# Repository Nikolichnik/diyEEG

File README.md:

# diyEEG
<h4>Attempt at building DIY EEG device.</h4>

<hr>

<p align="center">

</p>

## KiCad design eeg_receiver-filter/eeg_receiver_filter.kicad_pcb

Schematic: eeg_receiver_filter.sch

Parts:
C1: 10pF
C2: 330uF
C3, C6, C7, C8, C9, C10, C11, C12: 1nF
C4, C13, C14, C15, C16: 1uF
C5, C17: 3.3nF
D1: RedHiBr
J1: USB
L1: 70nH/60nH*
P1: eeg_out
P2: CONN_1
P3: RX_out
Q1, Q2: BFR92
R1: 100k
R2, R7, R10, R13, R15, R19, R20, R21, R24, R25: 1.5M
R3, R9, R11, R12: 10k
R4, R5: 3k6
R6: 1M1
R8, R14, R23, R28: 180k
R16, R17, R18, R22, R26, R27: 30k
R29: 2k
R30: 22k
R31: 20k
R32: 200k
R33: 47k
RV1: 10k
RV2: 100k
U1: TLC274CD
U2: TLC272CD

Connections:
+5V: J1.1 (Vbus), R9.1, R11.1, RV1.3, U1.4 (V+), U2.8 (V+)
GND: C4.2, C14.2, R30.1, U1.1, U1.2 (-), U1.10 (+), U1.12 (+), U2.5 (+)
GNDPWR: J1.4 (GND), P1.2 (PM), P3.2 (PM), Q1.1 (E), Q2.1 (E), R12.2, RV1.1, RV2.1, U1.11 (V-), U2.4 (V-)
unnamed: C10.2, C11.2, R21.2, R29.1, U2.1, U2.2 (-)
unnamed: R21.1, R22.1
unnamed: R25.2, R28.1
unnamed: R24.2, R25.1
unnamed: R20.2, R23.2
unnamed: C10.1, C11.1, R23.1, R24.1
unnamed: C12.2, R28.2, U2.3 (+)
unnamed: R26.2, R27.2
unnamed: R22.2, R26.1
unnamed: C5.1, C13.1, R5.2, U1.8
unnamed: C16.2, R33.1, U1.13 (-)
unnamed: R16.2, R17.1
unnamed: R19.2, R20.1
unnamed: C13.2, C15.1, C16.1, R30.2
unnamed: C9.1, C15.2, R19.1, R33.2, U1.14
unnamed: C3.2, C8.1, R18.1
unnamed: C9.2, C12.1, R27.1
unnamed: P1.1, RV2.2
unnamed: C17.2, R32.2, U2.6 (-)
unnamed: C14.1, R29.2, R31.1, R32.1
unnamed: C17.1, R31.2, RV2.3, U2.7
unnamed: C1.2, D1.2 (K), R1.1
unnamed: R3.2, R9.2
unnamed: R1.2, RV1.2
unnamed: C2.2, C3.1, P3.1, R2.1
unnamed: R11.2, R12.1, U1.3 (+)
unnamed: C5.2, R6.2, U1.9 (-)
unnamed: C4.1, R4.2, R5.1, R6.1
unnamed: C6.2, C7.2, R4.1, R15.2, U1.6 (-), U1.7
unnamed: R15.1, R16.1
unnamed: C6.1, C7.1
unnamed: C8.2, R14.2, U1.5 (+)
unnamed: R17.2, R18.2
unnamed: C1.1, C2.1, L1.2, P2.1, Q1.3 (C), Q2.2 (B), R3.1
unnamed: R2.2, R7.1
unnamed: D1.1 (A), L1.1, Q1.2 (B), Q2.3 (C)
unnamed: R13.2, R14.1
unnamed: R10.2, R13.1
unnamed: R8.1, R10.1
unnamed: R7.2, R8.2

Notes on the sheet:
Fosc=1/(2*Pi*sqrt(L*C)) ____________________________ Unit1: C=10 pF + LED (red, HiBr 5mm) LED- (5V -> 0V) -> (2pF -> 3.6pF) Ct=(1.67pF -> 5.65pF) L=70 nF (9T, 3 mm (W), 9 mm (L)) Fosc=(369MHz -> 467MHz)
|- notch Fc=50.08Hz Hz G=1 -|
|- LPF Fc=44 Hz G=-1 -|
|- HPF Fc=4.9 Hz G=-1 -|
|- LPF Fc=43.8 Hz G=-10 -|
P1- filtered out P2- RX antenna P3- RX out_test
Unit2: C=10 pF + LED (red, HiBr 5mm) LED- (5V -> 0V) -> (2pF -> 3.6pF) Ct=(1.67pF -> 5.65pF) L=60 nF (8T, 3 mm (W), 8 mm (L)) Fosc=(399MHz -> 502MHz)
Gt=-10
|- final output curve (?) -|

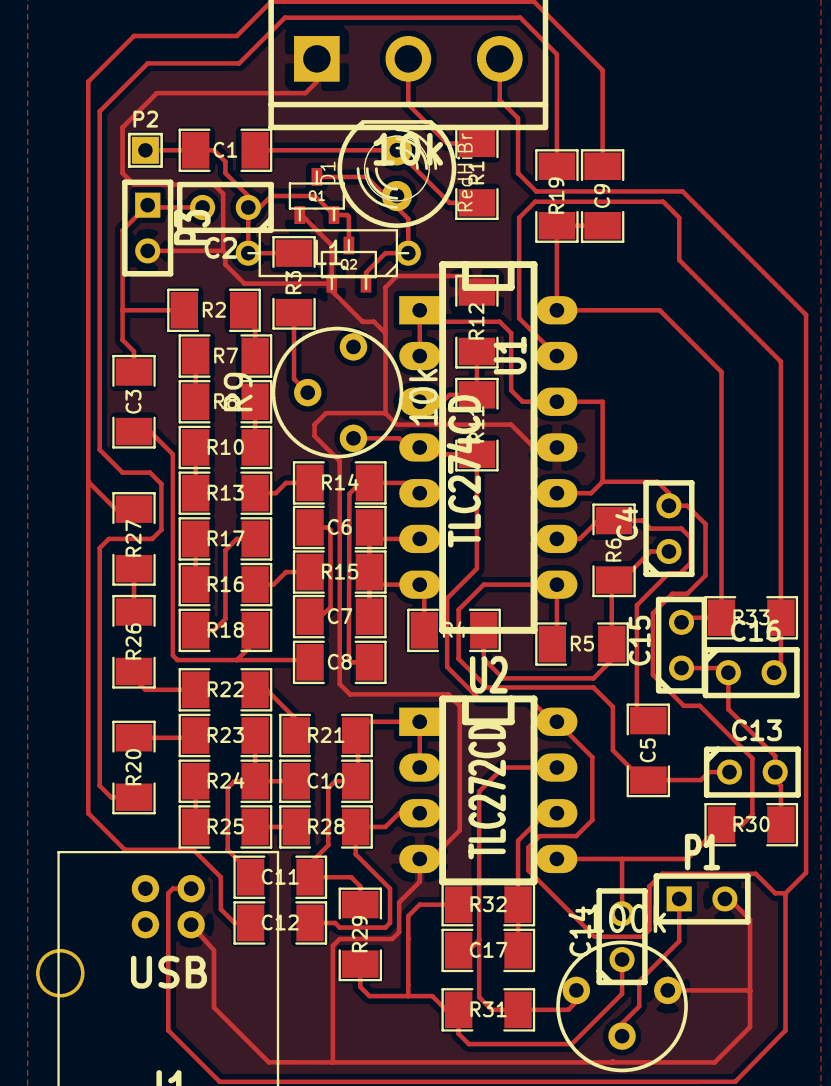
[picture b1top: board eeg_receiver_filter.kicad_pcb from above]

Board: 2 copper layers, 62 parts (0 on the bottom side), 43 nets.

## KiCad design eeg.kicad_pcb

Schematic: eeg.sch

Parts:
C1, C2: 0.1nF
C3, C7, C10: 1nF
C4: 1uF
C5: 3.3nF
C6: 330uF
C8: 1.2pF/1.5pF*
C9: 5pF
C11: 100uF
D1: 4.7V
D2: 1N4007
J1: USB
L1: 0.1uH/0.1uH*
P1, P2, P3, P4, P5, P6, P7, P8: CONN_1
Q1, Q2: BFR92
R1, R2: 5k6
R3: 150R
R4: 2k2
R5, R7: 470k
R6: 8k2
R8: 100k
R9: 330R
R10: 560R
R11, R12: 10k
SW1: reed_switch
SW2: slide
U1: AD623
U2: TLC272CD

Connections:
+BATT: C8.1, C10.1, L1.2, R8.2, R11.1, SW2.2, U1.7 (V+), U2.8 (V+)
GND: C1.2, C2.1, C4.2, U1.5 (Ref), U2.3 (+), U2.6 (-), U2.7
GNDPWR: C7.2, C10.2, C11.2, D1.1, J1.4 (GND), P4.1, P7.1, P8.1, R9.1, R12.2, U1.4 (V_), U2.4 (V-)
unnamed: C9.2, Q1.1 (E), R9.2
unnamed: C6.2, C7.1, Q1.2 (B), R8.1
unnamed: R11.2, R12.1, U2.5 (+)
unnamed: D2.2 (K), P6.1, SW2.1
unnamed: D2.1 (A), Q2.1 (E)
unnamed: C5.1, R5.2, SW1.1, U2.1
unnamed: P3.1, R7.1, SW1.2
unnamed: C8.2, C9.1, L1.1, P5.1, Q1.3 (C)
unnamed: J1.1 (Vbus), Q2.3 (C), R10.1
unnamed: C11.1, D1.2, Q2.2 (B), R10.2
unnamed: R4.1, U1.6 (OUT)
unnamed: C4.1, R4.2, R5.1, R6.1
unnamed: C5.2, R6.2, U2.2 (-)
unnamed: P2.1, R2.1
unnamed: C2.2, C3.2, R2.2, U1.2 (-)
unnamed: C1.1, C3.1, R1.2, U1.3 (+)
unnamed: P1.1, R1.1
unnamed: R3.1, U1.8 (Rg)
unnamed: R3.2, U1.1 (Rg)
unnamed: C6.1, R7.2

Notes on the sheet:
Fosc=1/(2*Pi*sqrt(L*C)) ____________________________ Unit1: C=1.5 pF L=0.1 uF Fosc= 410.936296 MHz Unit2: C=1.2 pF L=0.1 uF Fosc=459.440746 MHz -------------------------------- Unit1: C=47 pF L=3.124 nF (2T, 2 mm (W), 4 mm (L)) Fosc= 409.494 MHz Unit2: C=22 pF L=5.430 nF (2T, 2 mm (W), 2 mm (L)) Fo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
AD623: ---------------------- Rg=100k/(G-1) G=100k/Rg+1 Rg=150R G=667 INA122 ---------------------- Rg=200k/(G-5) G=200k/Rg+5 _____________________________________ Gt=-142738 Vin=10 uV->30 uV Vout=1.42 V->4.28 V
| LPF Fc=44.6 Hz G=-214(46.56dB) |
|RFI reject Fc=25836 Hz|
P1- electrode1 in P2- electrode2 in P3- audio inject signal P4- audio inject ground P5- antenna P6- batt+ P7- batt- P8- ground electrode in
| LPF Fc=44.6 Hz (?) G=-214 (46.56dB) |

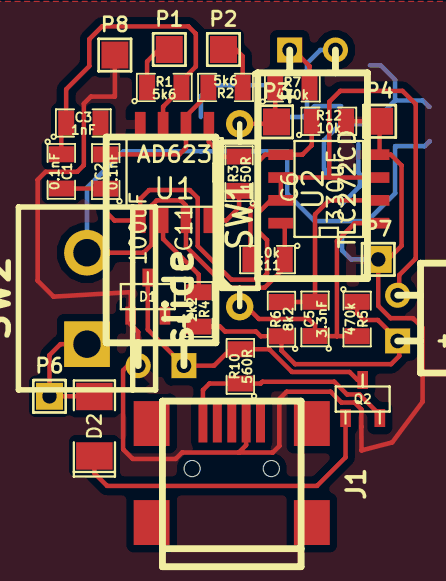
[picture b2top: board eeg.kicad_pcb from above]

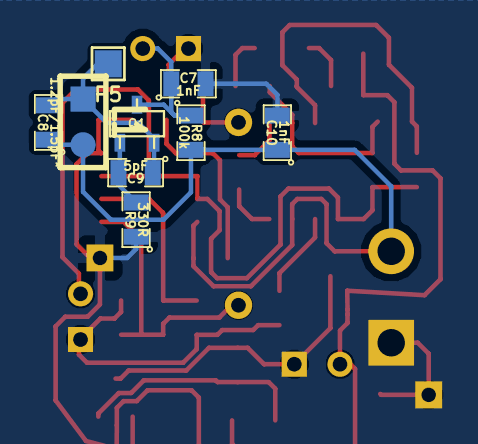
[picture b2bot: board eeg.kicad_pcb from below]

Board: 2 copper layers, 41 parts (9 on the bottom side), 23 nets.
